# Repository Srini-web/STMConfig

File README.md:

# STMConfig
## STM 32 Hardware Design and Custom Configuration using KiCad 7
The STM32 microcontroller model used here is the Blue Pill (STM32F103C8T6). It hosts the ARM Cortex M3 Microprocessor with a 32-bit RISC core operating at a 72 MHz frequency, and high-speed embedded memories. In this project, It has been interfaced with 
 + 1 USB (Micro-USB 2.0)
 + 1 UART line
 + 1 I2C2 line
 + Custom Oscillator
 + Regulator
   
#### Pin allocation and Power Configuration
There is a simple configuration performed therefore, although connected, the VBAT, and VDDA (Analog) are not actively used. To prevent power fluctuations and stabilize transitions, each Voltage source is provided with a decoupling capacitor and a bulk decoupling capacitor for all of them collectively. For the analog source, we need to provide an analog source linked to the collective VDD Supply. Since the analog voltage source is more sensitive, it is connected to a `ferrite bead ` of 120Ohm, 100MHz.

The `Reset` pin is connected to a pull-up circuit with a capacitor to prevent spurious resets. The `Boot0` pin used to enable or disable the upload and debugging of a program onto a board via the STMLINK is connected to a switch with a relatively high resistance.

##### Custom Oscillator
The `PD0` and `PD1` Pins are the oscillator i/o pins. For our custom oscillator, we have chosen the `SMD3225-4P` HSE(High-Speed External) Crystal Oscillator. Although the MCU has an in-built oscillator, an external oscillator not only provides better control and more precise clock speed but also enables the provision of a greater clock frequency. We have utilized it to provide greater frequency of `16MHz` using the oscillator.
Per the documentation, we connect two load capacitors whose value is determined by :-

```
CLoad = (Coscillator - CStray) * 2
CLoad = (10-5) *2 (stray capacitance ranges between 3 and 5 Farads)
CLoad = 10pF
```

##### USB
A Micro-USB (B) has been connected to the `PA11` and `PA12` pins which act as serial wire input and output pins. Specification is `STM: AN4879` . This circuitry is attached to a pull-up resistor circuit. 

##### Regulator
A regulator is required to filter the Input voltage provided through the `VBUS` input. This also serves as a power supply indicator using an LED in parallel. The specification is a linear resistor `AMS 3.3V` variant.

##### UART and I2C2
The UART and I2C2 pins are assigned to the `PB6`, `PB7`, and the `PB10`, `PB11` pins. The Pin assignment has been done using the STM32CubeIDE. After the assignment, the files are exported into KiCad. It is available in the `STM32F103C8T6_pinout.ioc` file. The clock circuitry generated also gives insights into the oscillator connection. A no connect `X` is attached to unused pins to avid ERC Violations.

### Schematic

During ERC, A power source conflict is created at the analog voltage source, Due to 2 conflicting voltage sources which can be avoided using a power flag.

### Footprint Assignment

Footprint assignment is done to ensure each component specification is done for PCB design and Manufacturing

### Planning (Layout)
It is a 2 layer board  into which the schematic footprints are imported and components are placed guided by the rat's nest links. Edge planning and mount holes are also added. Component labeling and notes are created using silkscreen. This is where the mount holes are also added, edge cuts are made defining board edges and the 3D model of the USB is appended to the footprint using the `629105150521 (rev1).stp` CAD file downloaded from the component site.

### Routing 
+ Path routing is essential and dependent on the efficiency of Planning. Two tracks have been used. Namely the 0.3 mm and 0.5 mm tracks. The smaller tracks are mostly used for signal routing and the larger/ broader track is used for power routing and ground vias.
+ Certain connects are connected by a power puddle during power routing. If this is not done properly, This may cause a copper imbalance leading to Tombstoning.

##### Signal Routing

##### Power Routing

##### 3D view after P&R

### Manufacturing
Following DRC clearance, to prepare the manufacturing model, the material list is generated from the schematic. After specifying and generating the drill hole list, The Gerber files are generated. All of these are available in the `Manufacturing` folder.

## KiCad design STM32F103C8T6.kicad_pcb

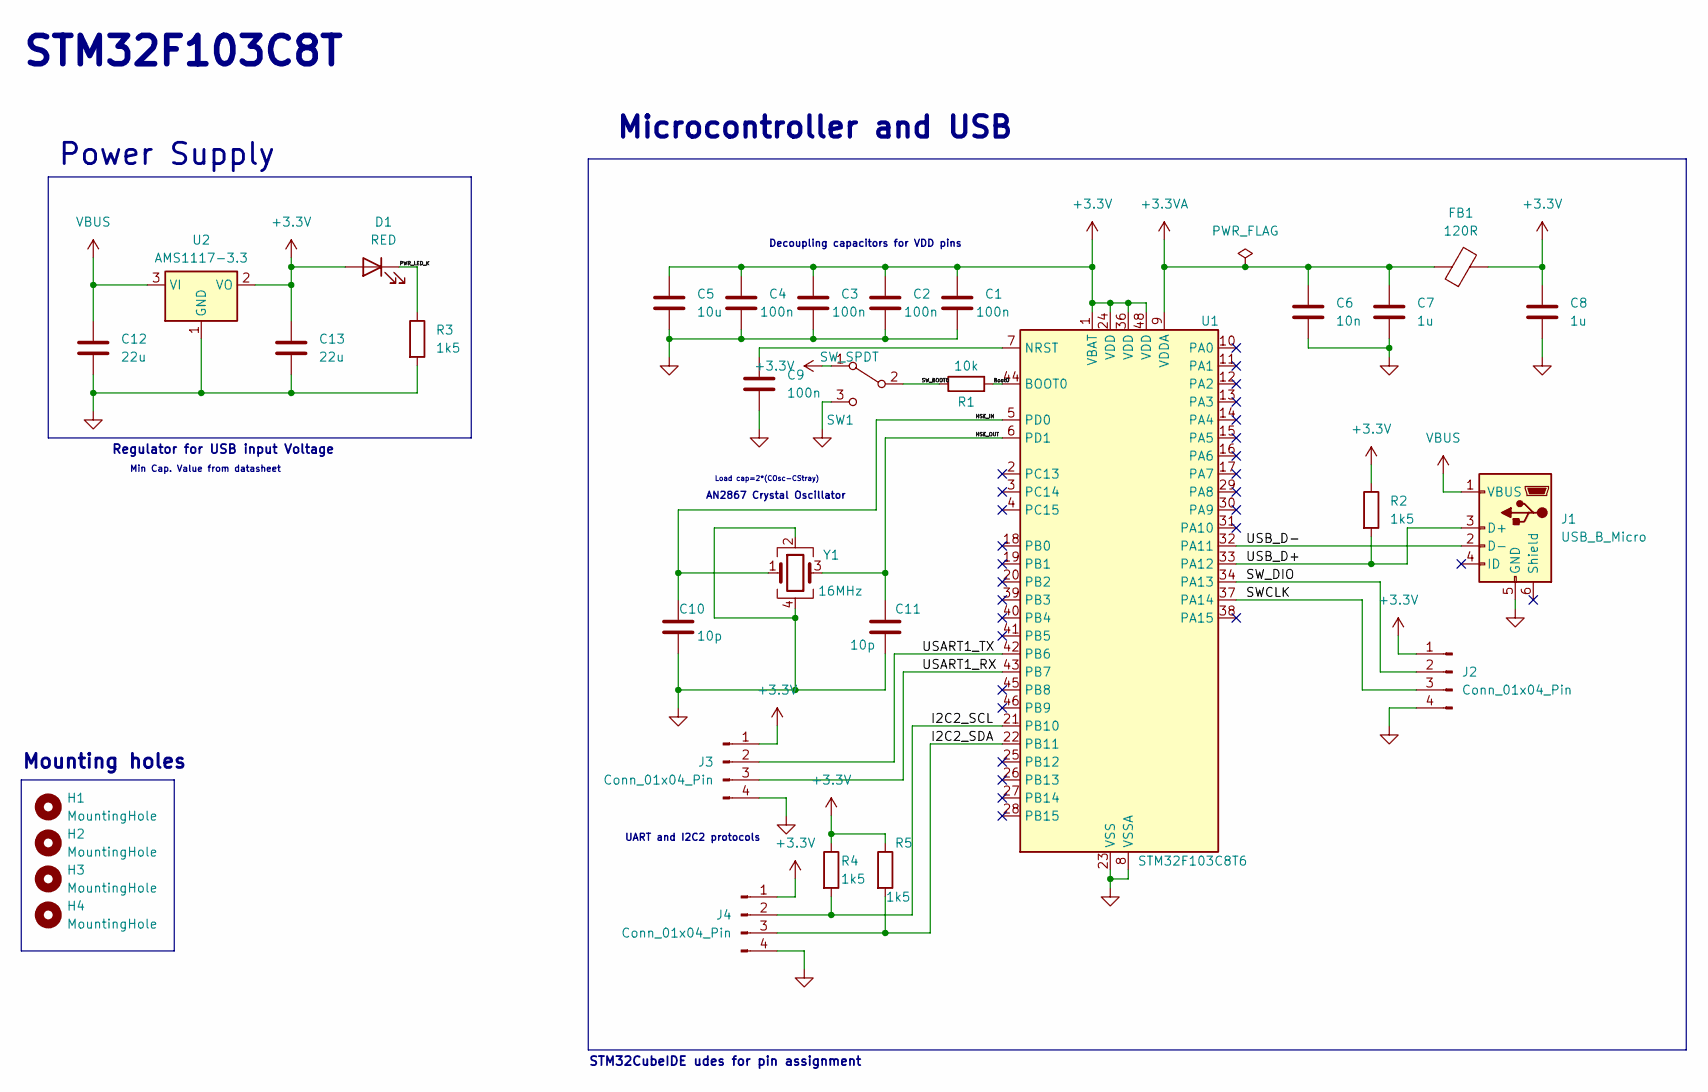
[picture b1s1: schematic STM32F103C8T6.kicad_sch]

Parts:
C1, C2, C3, C4, C9: 100n; C_0402_1005Metric
C5: 10u; C_0603_1608Metric
C6: 10n; C_0402_1005Metric
C7, C8: 1u; C_0402_1005Metric
C10, C11: 10p; C_0402_1005Metric
C12, C13: 22u; C_0805_2012Metric
D1: RED; LED_0603_1608Metric
FB1: 120R; L_0603_1608Metric
H1, H2, H3, H4: MountingHole; MountingHole_2.2mm_M2
J1: USB_B_Micro; USB_Micro-B_Wuerth_629105150521
J2, J3, J4: Conn_01x04_Pin; PinHeader_1x04_P2.54mm_Vertical
R1: 10k; R_0402_1005Metric
R2, R3, R4, R5: 1k5; R_0402_1005Metric
SW1: SW_SPDT; SW_SPDT_PCM12
U1: STM32F103C8T6; LQFP-48_7x7mm_P0.5mm
U2: AMS1117-3.3; SOT-223-3_TabPin2
Y1: 16MHz; Crystal_SMD_3225-4Pin_3.2x2.5mm

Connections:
+3.3V: C1.1, C2.1, C3.1, C4.1, C5.1, C8.1, C13.1, D1.2 (A), FB1.2, J2.1, J3.1, J4.1, R2.1, R4.1, R5.1, SW1.1 (A), U1.1 (VBAT), U1.24 (VDD), U1.36 (VDD), U1.48 (VDD), U2.2 (VO)
+3.3VA: C6.1, C7.1, FB1.1, U1.9 (VDDA)
/Boot0: R1.2, U1.44 (BOOT0)
/HSE_IN: C10.1, U1.5 (PD0), Y1.1
/HSE_OUT: C11.1, U1.6 (PD1), Y1.3
/I2C2_SCL: J4.2, R4.2, U1.21 (PB10)
/I2C2_SDA: J4.3, R5.2, U1.22 (PB11)
/PWR_LED_K: D1.1 (K), R3.1
/SWCLK: J2.3, U1.37 (PA14)
/SW_BOOT0: R1.1, SW1.2 (B)
/SW_DIO: J2.2, U1.34 (PA13)
/USART1_RX: J3.3, U1.43 (PB7)
/USART1_TX: J3.2, U1.42 (PB6)
/USB_D+: J1.3 (D+), R2.2, U1.33 (PA12)
/USB_D-: J1.2 (D-), U1.32 (PA11)
GND: C1.2, C2.2, C3.2, C4.2, C5.2, C6.2, C7.2, C8.2, C9.2, C10.2, C11.2, C12.2, C13.2, J1.5 (GND), J2.4, J3.4, J4.4, R3.2, SW1.3 (C), U1.8 (VSSA), U1.23 (VSS), U1.35 (VSS), U1.47 (VSS), U2.1 (GND), Y1.2, Y1.4
unnamed: C9.1, U1.7 (NRST)
VBUS: C12.1, J1.1 (VBUS), U2.3 (VI)

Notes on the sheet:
Decoupling capacitors for VDD pins
STM32F103C8T
Power Supply
AN2867 Crystal Oscillator
UART and I2C2 protocols
Regulator for USB input Voltage
Load cap=2*(COsc-CStray)
Mounting holes
Microcontroller and USB
STM32CubeIDE udes for pin assignment
Min Cap. Value from datasheet

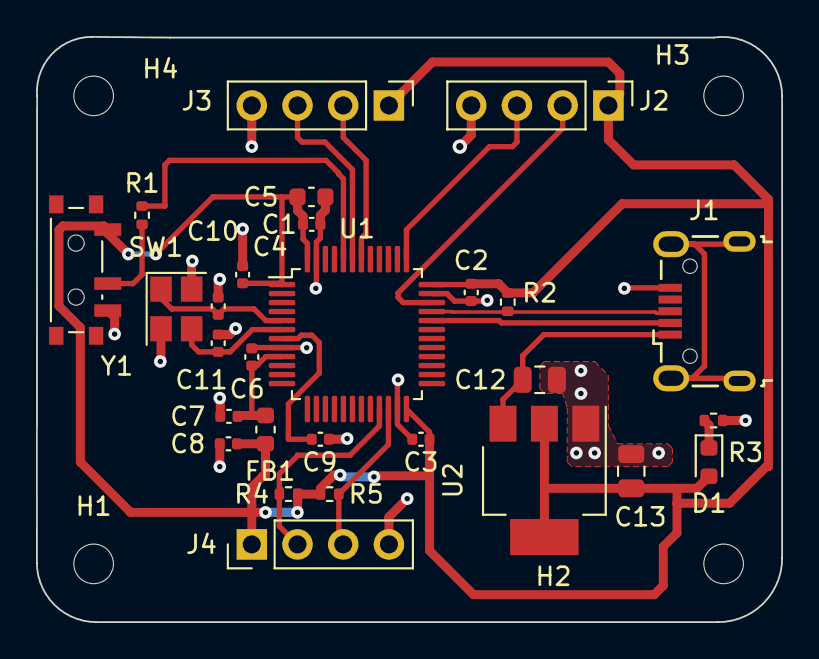
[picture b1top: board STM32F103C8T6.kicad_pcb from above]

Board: 2 copper layers, 41.4 x 32.5 mm, 32 parts (0 on the bottom side), 18 nets.

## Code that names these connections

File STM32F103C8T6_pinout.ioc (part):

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Mcu.Name=STM32F103C(8-B)Tx
Mcu.Package=LQFP48
Mcu.UserName=STM32F103C8Tx
PA11.Mode=Device
PA11.Signal=USB_DM
PA12.Mode=Device
PA12.Signal=USB_DP
PA13.Mode=Serial_Wire
PA13.Signal=SYS_JTMS-SWDIO
PA14.Mode=Serial_Wire
PA14.Signal=SYS_JTCK-SWCLK
PB10.Mode=I2C
PB10.Signal=I2C2_SCL
PB11.Mode=I2C
PB11.Signal=I2C2_SDA
PB6.Mode=Asynchronous
PB6.Signal=USART1_TX
PB7.Mode=Asynchronous
PB7.Signal=USART1_RX
PD0-OSC_IN.Mode=HSE-External-Oscillator
PD0-OSC_IN.Signal=RCC_OSC_IN
PD1-OSC_OUT.Mode=HSE-External-Oscillator
PD1-OSC_OUT.Signal=RCC_OSC_OUT
board=custom

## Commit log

2024-01-03 final upload
2024-01-03 ioc upload
